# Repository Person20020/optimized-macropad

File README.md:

# Optimized Macropad

This macropad is built to be in the shape of the optimized compact layout for 17 squares within a larger square. It has 17 keys with rgb backlights. It uses QMK Vial to allow the keys to be customized.

## PCB

There are two parts for the PCB. The main part holds the switches and the secondary small one allows the microcontroller to be attatched directly under in a more compact way.

PCB Layout

Schematic

## BOM

| Part                | Quantity | Price                      | Link                                                       |
| ------------------- | -------- | -------------------------- | ---------------------------------------------------------- |
| Seeed Xiao RP2040   | 1        | $10                        | [Amazon](https://a.co/d/aqcFIsh)                           |
| MX Switches         | 17       | ~$0.50 each = $8.50        |                                                            |
| 1n4148 Diodes       | 17       | $0.009 ea = $0.45 (50 min) | [LCSC](https://www.lcsc.com/product-detail/C402212.html)   |
| SK6812 Mini E LEDs  | 17       | $1.71                      | [LCSC](https://www.lcsc.com/product-detail/C5149201.html)  |
| Header Pins 1x7     | 2        | $0                         | Comes with Xiao                                            |
| Header Pins 1x6     | 2        | $0.25 (5 min order)        | [LCSC](https://www.lcsc.com/product-detail/C42431804.html) |
| m3x12 mm Screws     | 4        | $6.39 (pack of 120)        | [Amazon](https://a.co/d/36DvsYz)                           |
| m3 Heat Set Inserts | 4        | $5.59 (pack of 100)        | [Amazon](https://a.co/d/d310qRA)                           |
| Total Parts Price   |          | ~$32.89                    |                                                            |

PCBs cost $8.40.

Total cost: ~$41.29

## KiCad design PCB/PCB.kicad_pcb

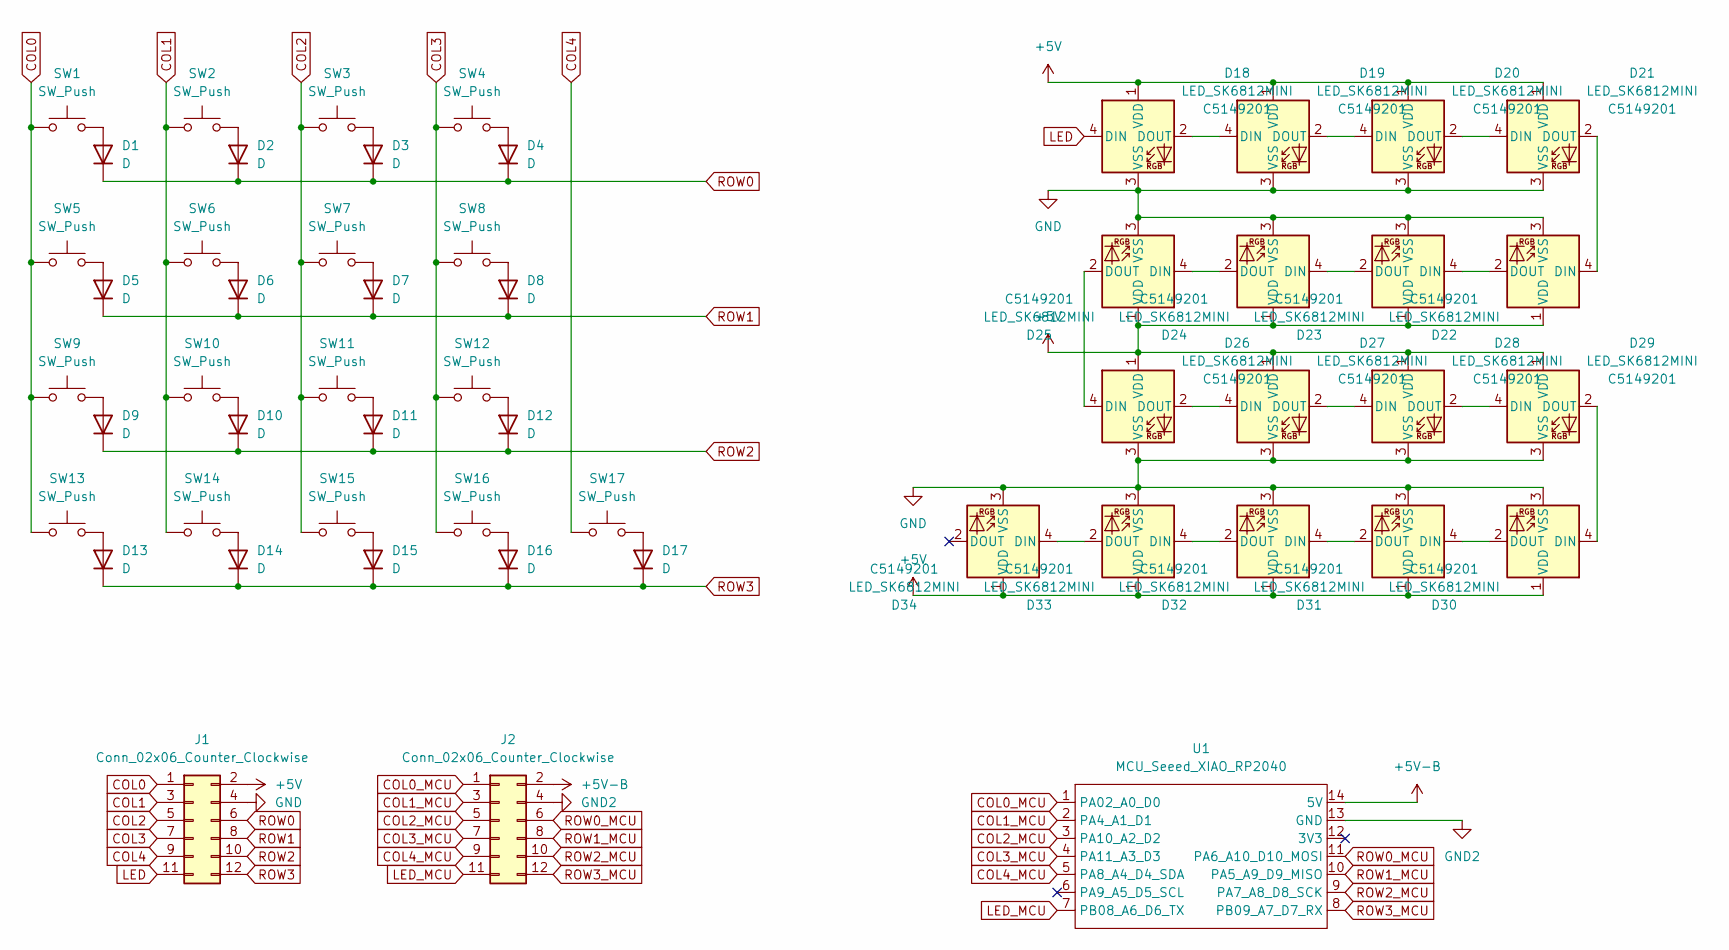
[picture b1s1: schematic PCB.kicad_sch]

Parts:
D1, D2, D3, D4, D5, D6, D7, D8, D9, D10, D11, D12, D13, D14, D15, D16, D17: D; D_DO-35_SOD27_P7.62mm_Horizontal
D18, D19, D20, D21, D22, D23, D24, D25, D26, D27, D28, D29, D30, D31, D32, D33, D34: LED_SK6812MINI; LCSC C5149201
J1, J2: Conn_02x06_Counter_Clockwise; PinHeader_2x06_P2.54mm_Vertical
SW1, SW2, SW3, SW4, SW5, SW6, SW7, SW8, SW9, SW10, SW11, SW12, SW13, SW14, SW15, SW16, SW17: SW_Push; MX_PCB_1.00u
U1: MCU_Seeed_XIAO_RP2040; Seeed_XIAO_RP2040

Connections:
+5V: D18.1 (VDD), D19.1 (VDD), D20.1 (VDD), D21.1 (VDD), D22.1 (VDD), D23.1 (VDD), D24.1 (VDD), D25.1 (VDD), D26.1 (VDD), D27.1 (VDD), D28.1 (VDD), D29.1 (VDD), D30.1 (VDD), D31.1 (VDD), D32.1 (VDD), D33.1 (VDD), D34.1 (VDD), J1.2
+5V-B: J2.2, U1.14 (5V)
COL0: J1.1, SW1.1, SW5.1, SW9.1, SW13.1
COL0_MCU: J2.1, U1.1 (PA02_A0_D0)
COL1: J1.3, SW2.1, SW6.1, SW10.1, SW14.1
COL1_MCU: J2.3, U1.2 (PA4_A1_D1)
COL2: J1.5, SW3.1, SW7.1, SW11.1, SW15.1
COL2_MCU: J2.5, U1.3 (PA10_A2_D2)
COL3: J1.7, SW4.1, SW8.1, SW12.1, SW16.1
COL3_MCU: J2.7, U1.4 (PA11_A3_D3)
COL4: J1.9, SW17.1
COL4_MCU: J2.9, U1.5 (PA8_A4_D4_SDA)
GND: D18.3 (VSS), D19.3 (VSS), D20.3 (VSS), D21.3 (VSS), D22.3 (VSS), D23.3 (VSS), D24.3 (VSS), D25.3 (VSS), D26.3 (VSS), D27.3 (VSS), D28.3 (VSS), D29.3 (VSS), D30.3 (VSS), D31.3 (VSS), D32.3 (VSS), D33.3 (VSS), D34.3 (VSS), J1.4
GND2: J2.4, U1.13 (GND)
LED: D18.4 (DIN), J1.11
LED_MCU: J2.11, U1.7 (PB08_A6_D6_TX)
unnamed: D1.2 (A), SW1.2
unnamed: D2.2 (A), SW2.2
unnamed: D3.2 (A), SW3.2
unnamed: D4.2 (A), SW4.2
unnamed: D5.2 (A), SW5.2
unnamed: D6.2 (A), SW6.2
unnamed: D7.2 (A), SW7.2
unnamed: D8.2 (A), SW8.2
unnamed: D9.2 (A), SW9.2
unnamed: D10.2 (A), SW10.2
unnamed: D11.2 (A), SW11.2
unnamed: D12.2 (A), SW12.2
unnamed: D13.2 (A), SW13.2
unnamed: D14.2 (A), SW14.2
unnamed: D15.2 (A), SW15.2
unnamed: D16.2 (A), SW16.2
unnamed: D17.2 (A), SW17.2
unnamed: D18.2 (DOUT), D19.4 (DIN)
unnamed: D19.2 (DOUT), D20.4 (DIN)
unnamed: D20.2 (DOUT), D21.4 (DIN)
unnamed: D21.2 (DOUT), D22.4 (DIN)
unnamed: D22.2 (DOUT), D23.4 (DIN)
unnamed: D23.2 (DOUT), D24.4 (DIN)
unnamed: D24.2 (DOUT), D25.4 (DIN)
unnamed: D25.2 (DOUT), D26.4 (DIN)
unnamed: D26.2 (DOUT), D27.4 (DIN)
unnamed: D27.2 (DOUT), D28.4 (DIN)
unnamed: D28.2 (DOUT), D29.4 (DIN)
unnamed: D29.2 (DOUT), D30.4 (DIN)
unnamed: D30.2 (DOUT), D31.4 (DIN)
unnamed: D31.2 (DOUT), D32.4 (DIN)
unnamed: D32.2 (DOUT), D33.4 (DIN)
unnamed: D33.2 (DOUT), D34.4 (DIN)
ROW0: D1.1 (K), D2.1 (K), D3.1 (K), D4.1 (K), J1.6
ROW0_MCU: J2.6, U1.11 (PA6_A10_D10_MOSI)
ROW1: D5.1 (K), D6.1 (K), D7.1 (K), D8.1 (K), J1.8
ROW1_MCU: J2.8, U1.10 (PA5_A9_D9_MISO)
ROW2: D9.1 (K), D10.1 (K), D11.1 (K), D12.1 (K), J1.10
ROW2_MCU: J2.10, U1.9 (PA7_A8_D8_SCK)
ROW3: D13.1 (K), D14.1 (K), D15.1 (K), D16.1 (K), D17.1 (K), J1.12
ROW3_MCU: J2.12, U1.8 (PB09_A7_D7_RX)

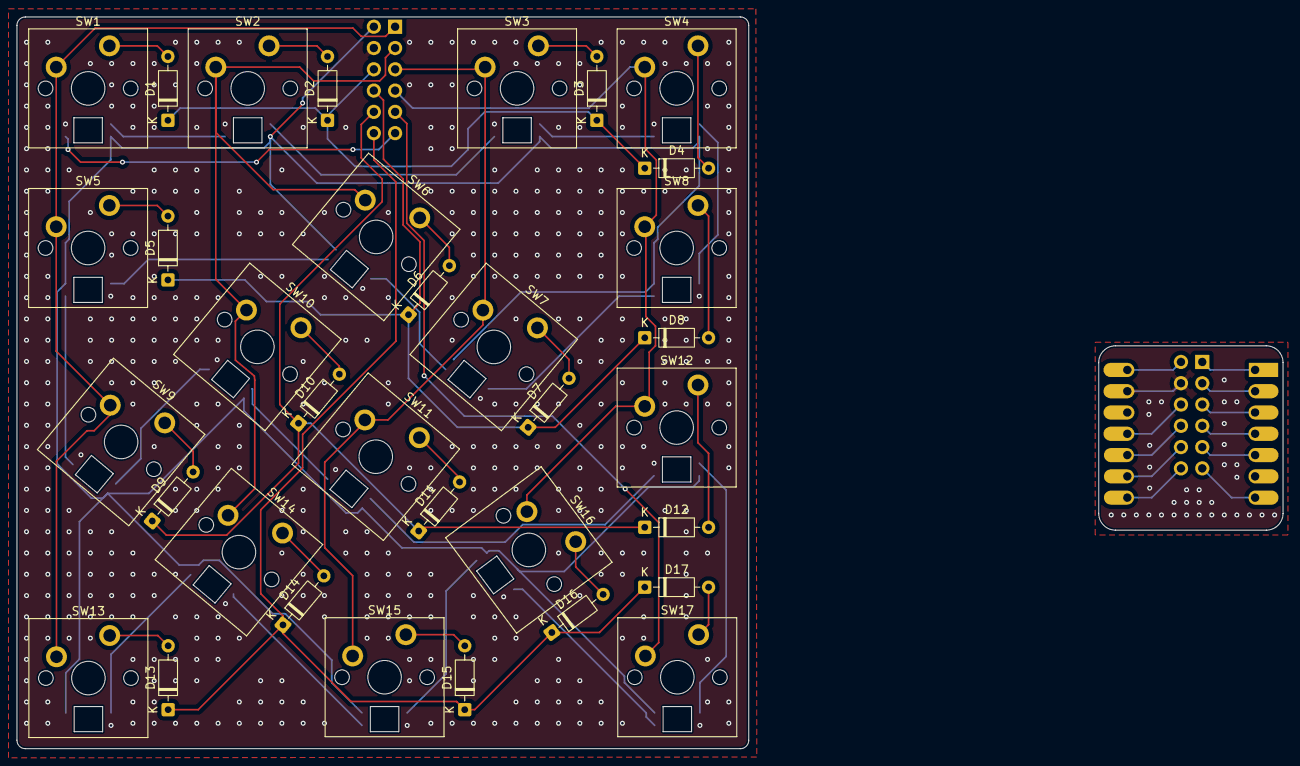
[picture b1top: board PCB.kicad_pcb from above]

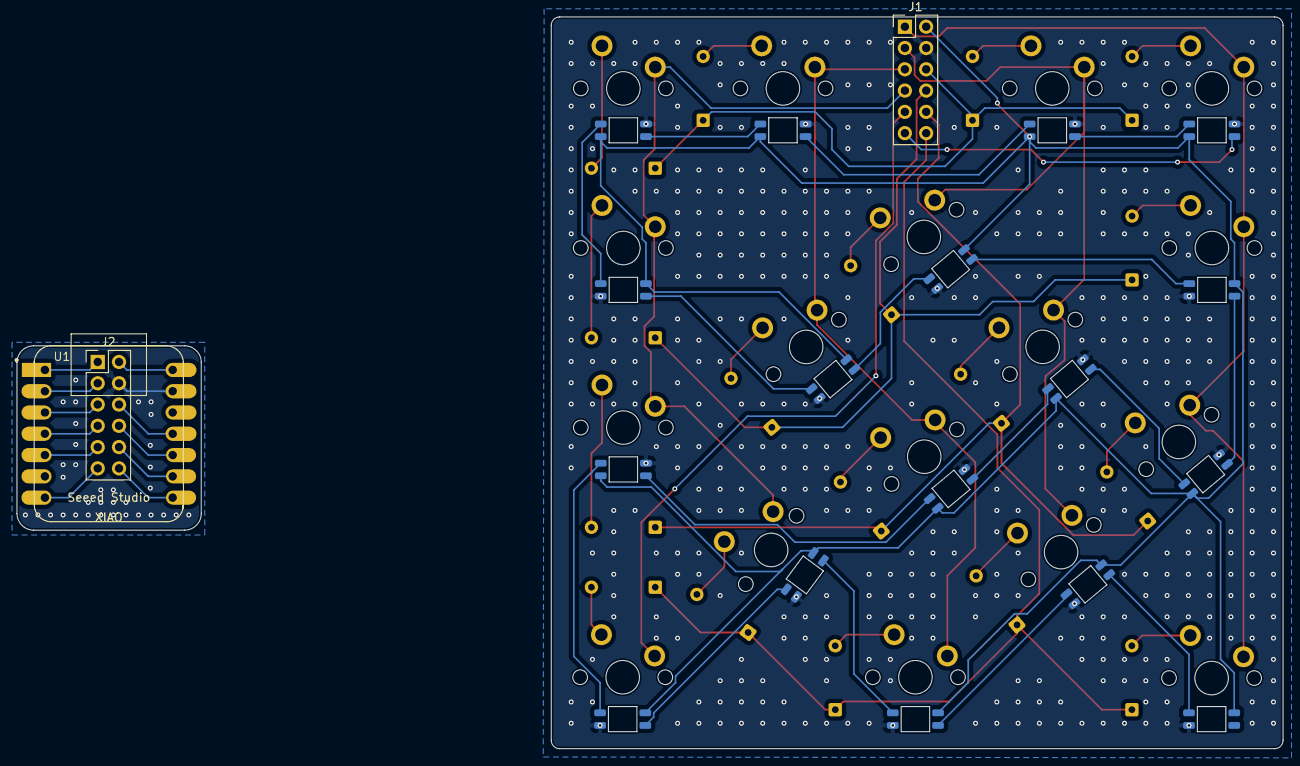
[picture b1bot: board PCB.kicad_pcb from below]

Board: 2 copper layers, 151.0 x 87.3 mm, 54 parts (20 on the bottom side), 57 nets.

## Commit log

2025-11-23 finished pcb + firmware
2025-11-24 added cad files and gerbers
2025-11-25 update readme with images
2025-12-02 add bom
2025-12-02 fix pcb price
